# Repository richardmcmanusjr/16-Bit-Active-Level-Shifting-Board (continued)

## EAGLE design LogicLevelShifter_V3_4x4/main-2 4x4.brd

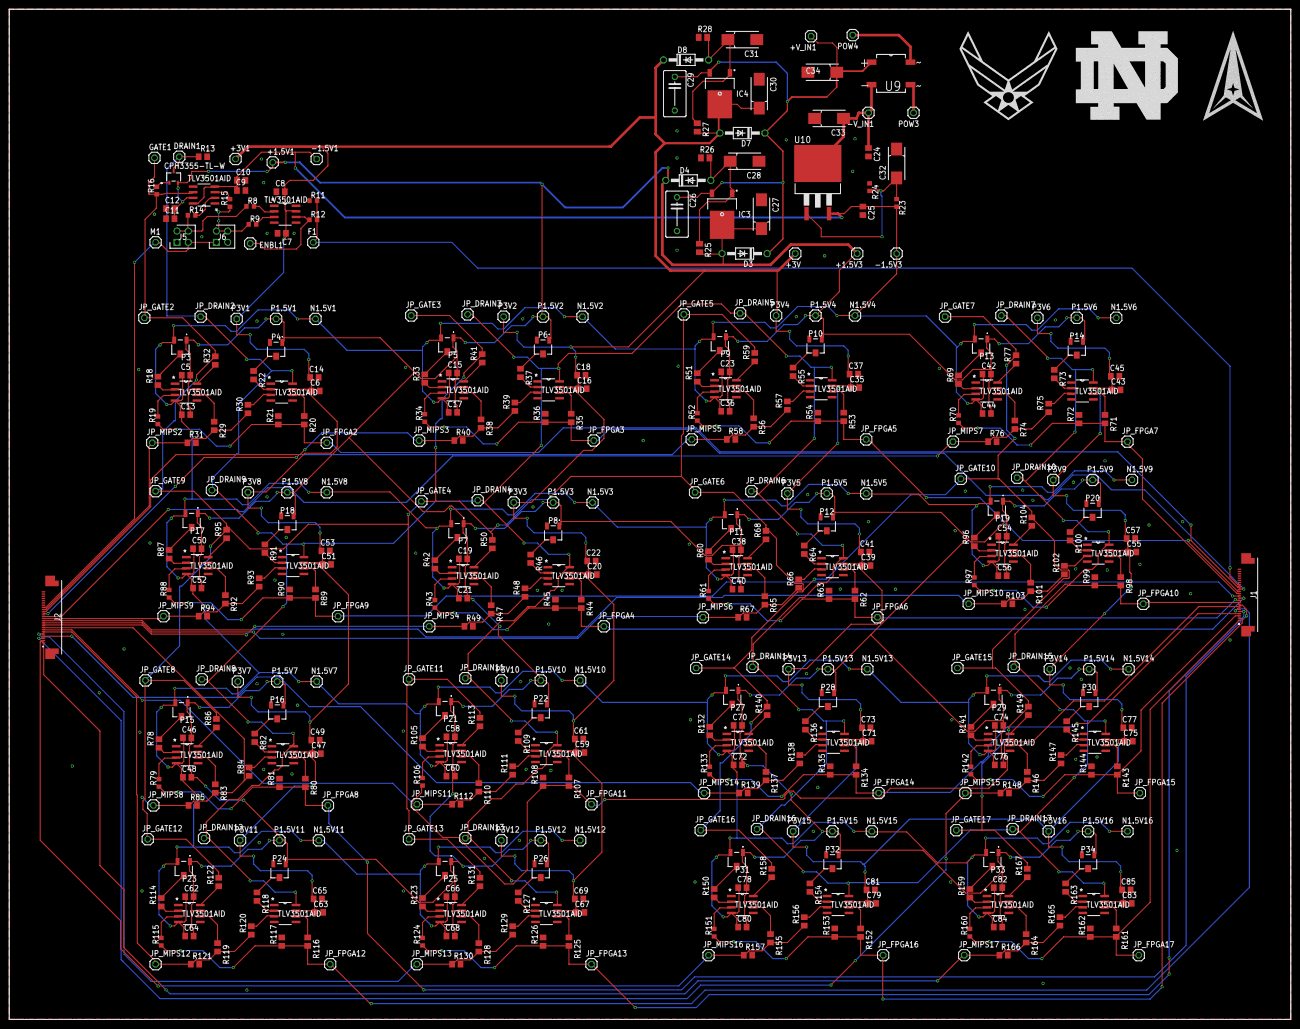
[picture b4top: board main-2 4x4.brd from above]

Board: 2 copper layers, 289.1 x 227.8 mm, 445 parts (0 on the bottom side), 199 nets.

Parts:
+1.5V1, +1.5V3, +3V, +3V1: 1X01
+V_IN1: 1X01
-1.5V1, -1.5V3: 1X01
-V_IN1: 1X01
C5, C6, C7, C8, C9, C10, C11, C12, C13, C14, C15, C16, C17, C18, C19, C20, C21, C22, C23, C35, C36, C37, C38, C39, C40, C41, C42, C43, C44, C45, C46, C47, C48, C49, C50, C51, C52, C53, C54, C55, C56, C57, C58, C59, C60, C61, C62, C63, C64, C65, C66, C67, C68, C69, C70, C71, C72, C73, C74, C75, C76, C77, C78, C79, C80, C81, C82, C83, C84, C85: C0805
C24: 10uF; C0805
C25: 0.1uF; C0805
C26, C29: 0.1uF; C075-052X106
C27, C30, C32: 1uF; 085CS_1AR
C28, C31, C33, C34: 10uF; 085CS_1AR
D3, D4, D7, D8: 1N4002; DO41-10
DRAIN1: 1X01
ENBL1: 1X01
F1: 1X01
GATE1: 1X01
IC3, IC4: LM317AMDT_NOPB; TO228P991X238-3N
J1, J2: 0524372471
J5, J6: 70287-1098; HDRV4W64P254_2X2_521X508X851P
JP_DRAIN2, JP_DRAIN3, JP_DRAIN4, JP_DRAIN5, JP_DRAIN6, JP_DRAIN7, JP_DRAIN8, JP_DRAIN9, JP_DRAIN10, JP_DRAIN11, JP_DRAIN12, JP_DRAIN13, JP_DRAIN14, JP_DRAIN15, JP_DRAIN16, JP_DRAIN17: 1X01
JP_FPGA2, JP_FPGA3, JP_FPGA4, JP_FPGA5, JP_FPGA6, JP_FPGA7, JP_FPGA8, JP_FPGA9, JP_FPGA10, JP_FPGA11, JP_FPGA12, JP_FPGA13, JP_FPGA14, JP_FPGA15, JP_FPGA16, JP_FPGA17: 1X01
JP_GATE2, JP_GATE3, JP_GATE4, JP_GATE5, JP_GATE6, JP_GATE7, JP_GATE8, JP_GATE9, JP_GATE10, JP_GATE11, JP_GATE12, JP_GATE13, JP_GATE14, JP_GATE15, JP_GATE16, JP_GATE17: 1X01
JP_MIPS2, JP_MIPS3, JP_MIPS4, JP_MIPS5, JP_MIPS6, JP_MIPS7, JP_MIPS8, JP_MIPS9, JP_MIPS10, JP_MIPS11, JP_MIPS12, JP_MIPS13, JP_MIPS14, JP_MIPS15, JP_MIPS16, JP_MIPS17: 1X01
M1: 1X01
N1.5V1, N1.5V2, N1.5V3, N1.5V4, N1.5V5, N1.5V6, N1.5V7, N1.5V8, N1.5V9, N1.5V10, N1.5V11, N1.5V12, N1.5V13, N1.5V14, N1.5V15, N1.5V16: 1X01
P1.5V1, P1.5V2, P1.5V3, P1.5V4, P1.5V5, P1.5V6, P1.5V7, P1.5V8, P1.5V9, P1.5V10, P1.5V11, P1.5V12, P1.5V13, P1.5V14, P1.5V15, P1.5V16, P3V1, P3V2, P3V3, P3V4, P3V5, P3V6, P3V7, P3V8, P3V9, P3V10, P3V11, P3V12, P3V13, P3V14, P3V15, P3V16: 1X01
P3, P4, P5, P6, P7, P8, P9, P10, P11, P12, P13, P14, P15, P16, P17, P18, P19, P20, P21, P22, P23, P24, P25, P26, P27, P28, P29, P30, P31, P32, P33, P34: SM-3TW102; SM3TW102
POW3, POW4: 1X01
R8, R9, R11, R12, R14, R15, R16: 220; R0603
R13: 51; R0805
R18, R22, R30, R33, R37, R39, R42, R46, R48, R51, R55, R57, R60, R64, R66, R69, R73, R75, R78, R82, R84, R87, R91, R93, R96, R100, R102, R105, R109, R111, R114, R118, R120, R123, R127, R129, R132, R136, R138, R141, R145, R147, R150, R154, R156, R159, R163, R165: 130; R0805
R19, R34, R43, R52, R61, R70, R79, R88, R97, R106, R115, R124, R133, R142, R151, R160: 130; R0603
R20, R21, R29, R31, R32, R35, R36, R38, R40, R41, R44, R45, R47, R49, R50, R53, R54, R56, R58, R59, R62, R63, R65, R67, R68, R71, R72, R74, R76, R77, R80, R81, R83, R85, R86, R89, R90, R92, R94, R95, R98, R99, R101, R103, R104, R107, R108, R110, R112, R113, R116, R117, R119, R121, R122, R125, R126, R128, R130, R131, R134, R135, R137, R139, R140, R143, R144, R146, R148, R149, R152, R153, R155, R157, R158, R161, R162, R164, R166, R167: 220; R0805
R23: 240; R0603
R24: 49.9; R0603
R25, R27: 240Ω; M0805
R26: 49Ω; M0805
R28: 390Ω; M0805
U3, U5, U6, U7, U8, U11, U12, U13, U14, U15, U16, U17, U18, U19, U20, U21, U22, U23, U24, U25, U26, U27, U28, U29, U30, U31, U32, U33, U34, U35, U36, U37, U38, U39: TLV3501AID; D8
U4: CPH3355-TL-W; CPH3_2P9X1P6_ONS
U9: DF10S; SOT508P985X260-4N
U10: MC79GENERICD2T; D2PAK-3

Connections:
+1.5V: +1.5V1.1, +1.5V3.1, C5.2, C11.2, C12.2, C13.2, C15.2, C17.2, C19.2, C21.2, C23.2, C27.+, C36.2, C38.2, C40.2, C42.2, C44.2, C46.2, C48.2, C50.2, C52.2, C54.2, C56.2, C58.2, C60.2, C62.2, C64.2, C66.2, C68.2, C70.2, C72.2, C74.2, C76.2, C78.2, C80.2, C82.2, C84.2, D3.A, D4.C, IC3.4, P1.5V1.1, P1.5V2.1, P1.5V3.1, P1.5V4.1, P1.5V5.1, P1.5V6.1, P1.5V7.1, P1.5V8.1, P1.5V9.1, P1.5V10.1, P1.5V11.1, P1.5V12.1, P1.5V13.1, P1.5V14.1, P1.5V15.1, P1.5V16.1, P3.1, P4.1, P5.1, P6.1, P7.1, P8.1, P9.1, P10.1, P11.1, P12.1, P13.1, P14.1, P15.1, P16.1, P17.1, P18.1, P19.1, P20.1, P21.1, P22.1, P23.1, P24.1, P25.1, P26.1, P27.1, P28.1, P29.1, P30.1, P31.1, P32.1, P33.1, P34.1, R25.2, U3.7, U4.2, U6.7, U8.7, U12.7, U14.7, U16.7, U18.7, U20.7, U22.7, U24.7, U26.7, U28.7, U30.7, U32.7, U34.7, U36.7, U38.7
+3V: +3V.1, +3V1.1, C6.1, C7.2, C8.2, C14.1, C16.1, C18.1, C20.1, C22.1, C30.+, C35.1, C37.1, C39.1, C41.1, C43.1, C45.1, C47.1, C49.1, C51.1, C53.1, C55.1, C57.1, C59.1, C61.1, C63.1, C65.1, C67.1, C69.1, C71.1, C73.1, C75.1, C77.1, C79.1, C81.1, C83.1, C85.1, D7.A, D8.C, IC4.4, P3V1.1, P3V2.1, P3V3.1, P3V4.1, P3V5.1, P3V6.1, P3V7.1, P3V8.1, P3V9.1, P3V10.1, P3V11.1, P3V12.1, P3V13.1, P3V14.1, P3V15.1, P3V16.1, R27.2, U5.7, U7.7, U11.7, U13.7, U15.7, U17.7, U19.7, U21.7, U23.7, U25.7, U27.7, U29.7, U31.7, U33.7, U35.7, U37.7, U39.7
-1.5V: -1.5V1.1, -1.5V3.1, C5.1, C9.1, C10.1, C13.1, C15.1, C17.1, C19.1, C21.1, C23.1, C25.1, C36.1, C38.1, C40.1, C42.1, C44.1, C46.1, C48.1, C50.1, C52.1, C54.1, C56.1, C58.1, C60.1, C62.1, C64.1, C66.1, C68.1, C70.1, C72.1, C74.1, C76.1, C78.1, C80.1, C82.1, C84.1, N1.5V1.1, N1.5V2.1, N1.5V3.1, N1.5V4.1, N1.5V5.1, N1.5V6.1, N1.5V7.1, N1.5V8.1, N1.5V9.1, N1.5V10.1, N1.5V11.1, N1.5V12.1, N1.5V13.1, N1.5V14.1, N1.5V15.1, N1.5V16.1, P3.3, P5.3, P7.3, P9.3, P11.3, P13.3, P15.3, P17.3, P19.3, P21.3, P23.3, P25.3, P27.3, P29.3, P31.3, P33.3, R23.2, U3.4, U6.4, U6.8, U8.4, U10.3, U12.4, U14.4, U16.4, U18.4, U20.4, U22.4, U24.4, U26.4, U28.4, U30.4, U32.4, U34.4, U36.4, U38.4
DIR_GATE: GATE1.1, JP_GATE2.1, JP_GATE3.1, JP_GATE4.1, JP_GATE5.1, JP_GATE6.1, JP_GATE7.1, JP_GATE8.1, JP_GATE9.1, JP_GATE10.1, JP_GATE11.1, JP_GATE12.1, JP_GATE13.1, JP_GATE14.1, JP_GATE15.1, JP_GATE16.1, JP_GATE17.1, R16.1, R32.2, R41.2, R50.2, R59.2, R68.2, R77.2, R86.2, R95.2, R104.2, R113.2, R122.2, R131.2, R140.2, R149.2, R158.2, R167.2, U6.6
F1: J1.1, JP_FPGA17.1, R160.1, R161.2, R162.1
F2: J1.2, JP_FPGA16.1, R151.1, R152.2, R153.1
F3: J1.3, JP_FPGA15.1, R142.1, R143.2, R144.1
F4: J1.4, JP_FPGA14.1, R133.1, R134.2, R135.1
F5: J1.5, JP_FPGA13.1, R124.1, R125.2, R126.1
F6: J1.6, JP_FPGA12.1, R115.1, R116.2, R117.1
F7: J1.7, JP_FPGA11.1, R106.1, R107.2, R108.1
F8: J1.8, JP_FPGA8.1, R79.1, R80.2, R81.1
F9: J1.9, JP_FPGA10.1, R97.1, R98.2, R99.1
F10: J1.10, JP_FPGA6.1, R61.1, R62.2, R63.1
F11: J1.11, JP_FPGA4.1, R43.1, R44.2, R45.1
F12: J1.12, JP_FPGA9.1, R88.1, R89.2, R90.1
F13: J1.13, JP_FPGA7.1, R70.1, R71.2, R72.1
F14: J1.14, JP_FPGA5.1, R52.1, R53.2, R54.1
F15: J1.15, JP_FPGA3.1, R34.1, R35.2, R36.1
F16: J1.16, JP_FPGA2.1, R19.1, R20.2, R21.1
F17: F1.1, J1.17, R11.2, R12.2
GND: C6.2, C7.1, C8.1, C9.2, C10.2, C11.1, C12.1, C14.2, C16.2, C18.2, C20.2, C22.2, C24.2, C25.2, C26.2, C27.-, C28.-, C29.2, C30.-, C31.-, C32.+, C33.+, C34.-, C35.2, C37.2, C39.2, C41.2, C43.2, C45.2, C47.2, C49.2, C51.2, C53.2, C55.2, C57.2, C59.2, C61.2, C63.2, C65.2, C67.2, C69.2, C71.2, C73.2, C75.2, C77.2, C79.2, C81.2, C83.2, C85.2, J1.MP1, J1.MP2, J1.MP3, J1.MP4, J2.MP1, J2.MP2, J2.MP3, J2.MP4, J5.1, J6.3, P4.3, P6.3, P8.3, P10.3, P12.3, P14.3, P16.3, P18.3, P20.3, P22.3, P24.3, P26.3, P28.3, P30.3, P32.3, P34.3, R11.1, R13.2, R21.2, R24.1, R26.1, R28.1, R31.2, R36.2, R40.2, R45.2, R49.2, R54.2, R58.2, R63.2, R67.2, R72.2, R76.2, R81.2, R85.2, R90.2, R94.2, R99.2, R103.2, R108.2, R112.2, R117.2, R121.2, R126.2, R130.2, R135.2, R139.2, R144.2, R148.2, R153.2, R157.2, R162.2, R166.2, U5.4, U5.8, U7.4, U11.4, U13.4, U15.4, U17.4, U19.4, U21.4, U23.4, U25.4, U27.4, U29.4, U31.4, U33.4, U35.4, U37.4, U39.4
INPPOS1: +V_IN1.1, C26.1, C29.1, C34.+, D3.C, D7.C, IC3.3, IC4.3, U9.1
INV_DIR_DRAIN: DRAIN1.1, JP_DRAIN2.1, JP_DRAIN3.1, JP_DRAIN4.1, JP_DRAIN5.1, JP_DRAIN6.1, JP_DRAIN7.1, JP_DRAIN8.1, JP_DRAIN9.1, JP_DRAIN10.1, JP_DRAIN11.1, JP_DRAIN12.1, JP_DRAIN13.1, JP_DRAIN14.1, JP_DRAIN15.1, JP_DRAIN16.1, JP_DRAIN17.1, R13.1, U4.3, U7.8, U11.8, U13.8, U15.8, U17.8, U19.8, U21.8, U23.8, U25.8, U27.8, U29.8, U31.8, U33.8, U35.8, U37.8, U39.8
IN_2: POW3.1, U9.3
M1: J2.1, JP_MIPS17.1, R164.2, R165.1, R166.1
M2: J2.2, JP_MIPS16.1, R155.2, R156.1, R157.1
M3: J2.3, JP_MIPS15.1, R146.2, R147.1, R148.1
M4: J2.4, JP_MIPS14.1, R137.2, R138.1, R139.1
M5: J2.5, JP_MIPS13.1, R128.2, R129.1, R130.1
M6: J2.6, JP_MIPS12.1, R119.2, R120.1, R121.1
M7: J2.7, JP_MIPS11.1, R110.2, R111.1, R112.1
M8: J2.8, JP_MIPS8.1, R83.2, R84.1, R85.1
M9: J2.9, JP_MIPS10.1, R101.2, R102.1, R103.1
M10: J2.10, JP_MIPS6.1, R65.2, R66.1, R67.1
M11: J2.11, JP_MIPS4.1, R47.2, R48.1, R49.1
M12: J2.12, JP_MIPS9.1, R92.2, R93.1, R94.1
M13: J2.13, JP_MIPS7.1, R74.2, R75.1, R76.1
M14: J2.14, JP_MIPS5.1, R56.2, R57.1, R58.1
M15: J2.15, JP_MIPS3.1, R38.2, R39.1, R40.1
M16: J2.16, JP_MIPS2.1, R29.2, R30.1, R31.1
M17: J2.17, J5.3, J6.1, M1.1
unnamed: P3.2, R18.2
unnamed: R18.1, U3.2
unnamed: R19.2, U3.3
unnamed: R20.1, U7.6
unnamed: P4.2, R22.1
unnamed: R22.2, U7.2
unnamed: R8.2, U5.2
unnamed: R30.2, U7.3
unnamed: R9.2, U5.3
unnamed: ENBL1.1, R12.1, U5.6
unnamed: J6.2, J6.4, R9.1, R15.1
unnamed: J5.2, J5.4, R8.1, R14.1
unnamed: R14.2, U6.2
unnamed: R15.2, U6.3
unnamed: R16.2, U4.1
unnamed: R29.1, U3.6
unnamed: R32.1, U3.8
unnamed: P5.2, R33.2
unnamed: R33.1, U8.2
unnamed: R34.2, U8.3
unnamed: C32.-, R23.1, R24.2, U10.1
unnamed: C28.+, D4.A, IC3.1, R25.1, R26.2
unnamed: C31.+, D8.A, IC4.1, R27.1, R28.2
unnamed: POW4.1, U9.4
unnamed: -V_IN1.1, C24.1, C33.-, U9.2, U10.4
unnamed: R35.1, U11.6
unnamed: P6.2, R37.1
unnamed: R37.2, U11.2
unnamed: R39.2, U11.3
unnamed: R38.1, U8.6
unnamed: R41.1, U8.8
unnamed: P7.2, R42.2
unnamed: R42.1, U12.2
unnamed: R43.2, U12.3
unnamed: R44.1, U13.6
unnamed: P8.2, R46.1
unnamed: R46.2, U13.2
unnamed: R48.2, U13.3
unnamed: R47.1, U12.6
unnamed: R50.1, U12.8
unnamed: P9.2, R51.2
unnamed: R51.1, U14.2
unnamed: R52.2, U14.3
unnamed: R53.1, U15.6
unnamed: P10.2, R55.1
unnamed: R55.2, U15.2
unnamed: R57.2, U15.3
unnamed: R56.1, U14.6
unnamed: R59.1, U14.8
unnamed: P11.2, R60.2
unnamed: R60.1, U16.2
unnamed: R61.2, U16.3
unnamed: R62.1, U17.6
unnamed: P12.2, R64.1
unnamed: R64.2, U17.2
unnamed: R66.2, U17.3
unnamed: R65.1, U16.6
unnamed: R68.1, U16.8
unnamed: P13.2, R69.2
unnamed: R69.1, U18.2
unnamed: R70.2, U18.3
unnamed: R71.1, U19.6
unnamed: P14.2, R73.1
unnamed: R73.2, U19.2
unnamed: R75.2, U19.3
unnamed: R74.1, U18.6
unnamed: R77.1, U18.8
unnamed: P15.2, R78.2
unnamed: R78.1, U20.2
unnamed: R79.2, U20.3
unnamed: R80.1, U21.6
unnamed: P16.2, R82.1
unnamed: R82.2, U21.2
unnamed: R84.2, U21.3
unnamed: R83.1, U20.6
unnamed: R86.1, U20.8
unnamed: P17.2, R87.2
unnamed: R87.1, U22.2
unnamed: R88.2, U22.3
unnamed: R89.1, U23.6
unnamed: P18.2, R91.1
unnamed: R91.2, U23.2
unnamed: R93.2, U23.3
unnamed: R92.1, U22.6
unnamed: R95.1, U22.8
unnamed: P19.2, R96.2
unnamed: R96.1, U24.2
unnamed: R97.2, U24.3
unnamed: R98.1, U25.6
unnamed: P20.2, R100.1
unnamed: R100.2, U25.2
unnamed: R102.2, U25.3
unnamed: R101.1, U24.6
unnamed: R104.1, U24.8
unnamed: P21.2, R105.2
unnamed: R105.1, U26.2
unnamed: R106.2, U26.3
unnamed: R107.1, U27.6
unnamed: P22.2, R109.1
unnamed: R109.2, U27.2
unnamed: R111.2, U27.3
unnamed: R110.1, U26.6
unnamed: R113.1, U26.8
unnamed: P23.2, R114.2
unnamed: R114.1, U28.2
unnamed: R115.2, U28.3
unnamed: R116.1, U29.6
unnamed: P24.2, R118.1
unnamed: R118.2, U29.2
unnamed: R120.2, U29.3
unnamed: R119.1, U28.6
unnamed: R122.1, U28.8
unnamed: P25.2, R123.2
unnamed: R123.1, U30.2
unnamed: R124.2, U30.3
unnamed: R125.1, U31.6
unnamed: P26.2, R127.1
unnamed: R127.2, U31.2
unnamed: R129.2, U31.3
unnamed: R128.1, U30.6
unnamed: R131.1, U30.8
unnamed: P27.2, R132.2
unnamed: R132.1, U32.2
unnamed: R133.2, U32.3
unnamed: R134.1, U33.6
unnamed: P28.2, R136.1
unnamed: R136.2, U33.2
unnamed: R138.2, U33.3
unnamed: R137.1, U32.6
unnamed: R140.1, U32.8
unnamed: P29.2, R141.2
unnamed: R141.1, U34.2
unnamed: R142.2, U34.3
unnamed: R143.1, U35.6
unnamed: P30.2, R145.1
unnamed: R145.2, U35.2
unnamed: R147.2, U35.3
unnamed: R146.1, U34.6
unnamed: R149.1, U34.8
unnamed: P31.2, R150.2
unnamed: R150.1, U36.2
unnamed: R151.2, U36.3
unnamed: R152.1, U37.6
unnamed: P32.2, R154.1
unnamed: R154.2, U37.2
unnamed: R156.2, U37.3
unnamed: R155.1, U36.6
unnamed: R158.1, U36.8
unnamed: P33.2, R159.2
unnamed: R159.1, U38.2
unnamed: R160.2, U38.3
unnamed: R161.1, U39.6
unnamed: P34.2, R163.1
unnamed: R163.2, U39.2
unnamed: R165.2, U39.3
unnamed: R164.1, U38.6
unnamed: R167.1, U38.8

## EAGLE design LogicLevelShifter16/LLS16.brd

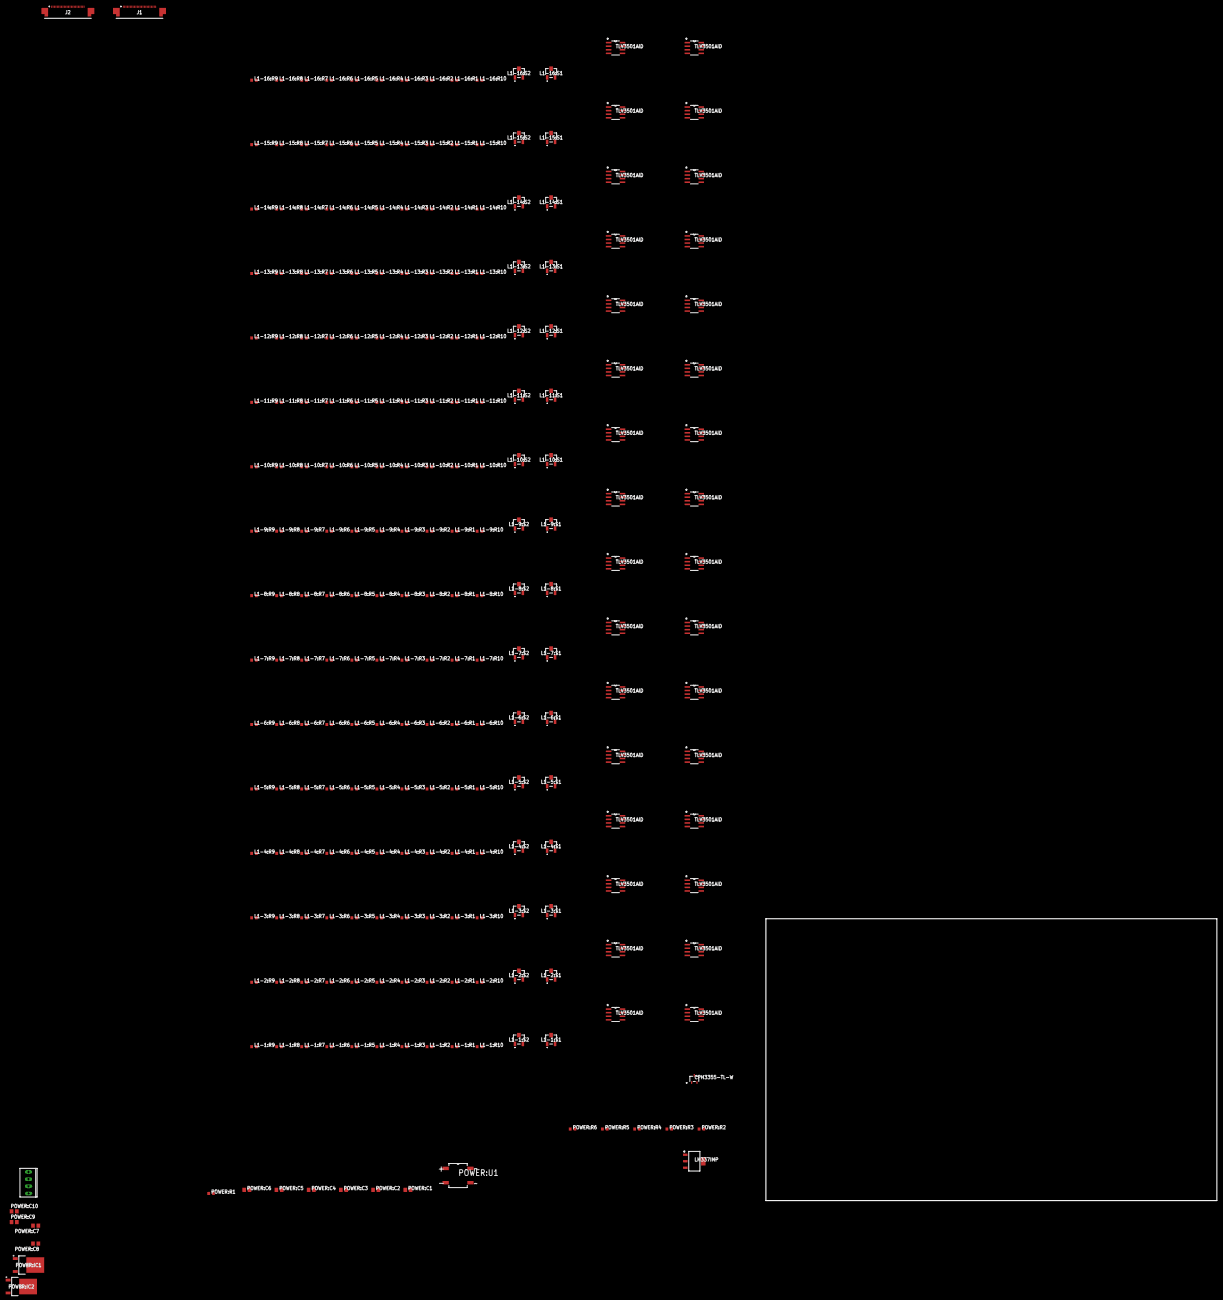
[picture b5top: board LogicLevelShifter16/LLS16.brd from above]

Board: 2 copper layers, 160.0 x 100.0 mm, 248 parts (0 on the bottom side), 204 nets, no tracks yet.

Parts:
J1, J2: 0524372471
L1-1:R1, L1-1:R2, L1-1:R6, L1-1:R8, L1-2:R1, L1-2:R2, L1-2:R6, L1-2:R8, L1-3:R1, L1-3:R2, L1-3:R6, L1-3:R8, L1-4:R1, L1-4:R2, L1-4:R6, L1-4:R8, L1-5:R1, L1-5:R2, L1-5:R6, L1-5:R8, L1-6:R1, L1-6:R2, L1-6:R6, L1-6:R8, L1-7:R1, L1-7:R2, L1-7:R6, L1-7:R8, L1-8:R1, L1-8:R2, L1-8:R6, L1-8:R8, L1-9:R1, L1-9:R2, L1-9:R6, L1-9:R8, L1-10:R1, L1-10:R2, L1-10:R6, L1-10:R8, L1-11:R1, L1-11:R2, L1-11:R6, L1-11:R8, L1-12:R1, L1-12:R2, L1-12:R6, L1-12:R8, L1-13:R1, L1-13:R2, L1-13:R6, L1-13:R8, L1-14:R1, L1-14:R2, L1-14:R6, L1-14:R8, L1-15:R1, L1-15:R2, L1-15:R6, L1-15:R8, L1-16:R1, L1-16:R2, L1-16:R6, L1-16:R8: 130; R0603
L1-1:R3, L1-1:R4, L1-1:R7, L1-1:R9, L1-1:R10, L1-2:R3, L1-2:R4, L1-2:R7, L1-2:R9, L1-2:R10, L1-3:R3, L1-3:R4, L1-3:R7, L1-3:R9, L1-3:R10, L1-4:R3, L1-4:R4, L1-4:R7, L1-4:R9, L1-4:R10, L1-5:R3, L1-5:R4, L1-5:R7, L1-5:R9, L1-5:R10, L1-6:R3, L1-6:R4, L1-6:R7, L1-6:R9, L1-6:R10, L1-7:R3, L1-7:R4, L1-7:R7, L1-7:R9, L1-7:R10, L1-8:R3, L1-8:R4, L1-8:R7, L1-8:R9, L1-8:R10, L1-9:R3, L1-9:R4, L1-9:R7, L1-9:R9, L1-9:R10, L1-10:R3, L1-10:R4, L1-10:R7, L1-10:R9, L1-10:R10, L1-11:R3, L1-11:R4, L1-11:R7, L1-11:R9, L1-11:R10, L1-12:R3, L1-12:R4, L1-12:R7, L1-12:R9, L1-12:R10, L1-13:R3, L1-13:R4, L1-13:R7, L1-13:R9, L1-13:R10, L1-14:R3, L1-14:R4, L1-14:R7, L1-14:R9, L1-14:R10, L1-15:R3, L1-15:R4, L1-15:R7, L1-15:R9, L1-15:R10, L1-16:R3, L1-16:R4, L1-16:R7, L1-16:R9, L1-16:R10: 220; R0603
L1-1:R5, L1-2:R5, L1-3:R5, L1-4:R5, L1-5:R5, L1-6:R5, L1-7:R5, L1-8:R5, L1-9:R5, L1-10:R5, L1-11:R5, L1-12:R5, L1-13:R5, L1-14:R5, L1-15:R5, L1-16:R5: 51; R0603
L1-1:S1, L1-1:S2, L1-2:S1, L1-2:S2, L1-3:S1, L1-3:S2, L1-4:S1, L1-4:S2, L1-5:S1, L1-5:S2, L1-6:S1, L1-6:S2, L1-7:S1, L1-7:S2, L1-8:S1, L1-8:S2, L1-9:S1, L1-9:S2, L1-10:S1, L1-10:S2, L1-11:S1, L1-11:S2, L1-12:S1, L1-12:S2, L1-13:S1, L1-13:S2, L1-14:S1, L1-14:S2, L1-15:S1, L1-15:S2, L1-16:S1, L1-16:S2: SM-3TW102; SM3TW102
L1-1:U1, L1-1:U2, L1-2:U1, L1-2:U2, L1-3:U1, L1-3:U2, L1-4:U1, L1-4:U2, L1-5:U1, L1-5:U2, L1-6:U1, L1-6:U2, L1-7:U1, L1-7:U2, L1-8:U1, L1-8:U2, L1-9:U1, L1-9:U2, L1-10:U1, L1-10:U2, L1-11:U1, L1-11:U2, L1-12:U1, L1-12:U2, L1-13:U1, L1-13:U2, L1-14:U1, L1-14:U2, L1-15:U1, L1-15:U2, L1-16:U1, L1-16:U2: TLV3501AID; D8
POWER:C1, POWER:C2, POWER:C3: 10uF; C0805
POWER:C4, POWER:C5, POWER:C6: 0.1uF; C0805
POWER:C7, POWER:C9: 0.1 uF; C0805
POWER:C8, POWER:C10: 2.2 uF; C0805
POWER:IC1, POWER:IC2: LM317AMDT_NOPB; TO228P991X238-3N
POWER:R1, POWER:R3, POWER:R5: 240; R0603
POWER:R2, POWER:R4, POWER:R6: 49.9; R0603
POWER:U1: DF10S; SOT508P985X260-4N
POWER:U2: LM337IMP; MP04A_TEX
U1: CPH3355-TL-W; CPH3_2P9X1P6_ONS
U$1: CONNHEADERVERT4POS2.54MM

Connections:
+1.5V: L1-1:S1.3, L1-1:S2.1, L1-1:U1.7, L1-2:S1.3, L1-2:S2.1, L1-2:U1.7, L1-3:S1.3, L1-3:S2.1, L1-3:U1.7, L1-4:S1.3, L1-4:S2.1, L1-4:U1.7, L1-5:S1.3, L1-5:S2.1, L1-5:U1.7, L1-6:S1.3, L1-6:S2.1, L1-6:U1.7, L1-7:S1.3, L1-7:S2.1, L1-7:U1.7, L1-8:S1.3, L1-8:S2.1, L1-8:U1.7, L1-9:S1.3, L1-9:S2.1, L1-9:U1.7, L1-10:S1.3, L1-10:S2.1, L1-10:U1.7, L1-11:S1.3, L1-11:S2.1, L1-11:U1.7, L1-12:S1.3, L1-12:S2.1, L1-12:U1.7, L1-13:S1.3, L1-13:S2.1, L1-13:U1.7, L1-14:S1.3, L1-14:S2.1, L1-14:U1.7, L1-15:S1.3, L1-15:S2.1, L1-15:U1.7, L1-16:S1.3, L1-16:S2.1, L1-16:U1.7, POWER:C5.1, POWER:C9.1, POWER:C10.1, POWER:IC1.4, POWER:R3.2, U1.2
+3V: L1-1:U2.7, L1-2:U2.7, L1-3:U2.7, L1-4:U2.7, L1-5:U2.7, L1-6:U2.7, L1-7:U2.7, L1-8:U2.7, L1-9:U2.7, L1-10:U2.7, L1-11:U2.7, L1-12:U2.7, L1-13:U2.7, L1-14:U2.7, L1-15:U2.7, L1-16:U2.7, POWER:C6.1, POWER:C7.1, POWER:C8.1, POWER:IC2.4, POWER:R5.2
+5V: POWER:U1.4, U$1.4
-1.5V: L1-1:S1.1, L1-1:U1.4, L1-2:S1.1, L1-2:U1.4, L1-3:S1.1, L1-3:U1.4, L1-4:S1.1, L1-4:U1.4, L1-5:S1.1, L1-5:U1.4, L1-6:S1.1, L1-6:U1.4, L1-7:S1.1, L1-7:U1.4, L1-8:S1.1, L1-8:U1.4, L1-9:S1.1, L1-9:U1.4, L1-10:S1.1, L1-10:U1.4, L1-11:S1.1, L1-11:U1.4, L1-12:S1.1, L1-12:U1.4, L1-13:S1.1, L1-13:U1.4, L1-14:S1.1, L1-14:U1.4, L1-15:S1.1, L1-15:U1.4, L1-16:S1.1, L1-16:U1.4, POWER:C4.1, POWER:C9.2, POWER:C10.2, POWER:R1.2, POWER:U2.3
D: L1-1:R5.1, L1-1:U2.8, L1-2:R5.1, L1-2:U2.8, L1-3:R5.1, L1-3:U2.8, L1-4:R5.1, L1-4:U2.8, L1-5:R5.1, L1-5:U2.8, L1-6:R5.1, L1-6:U2.8, L1-7:R5.1, L1-7:U2.8, L1-8:R5.1, L1-8:U2.8, L1-9:R5.1, L1-9:U2.8, L1-10:R5.1, L1-10:U2.8, L1-11:R5.1, L1-11:U2.8, L1-12:R5.1, L1-12:U2.8, L1-13:R5.1, L1-13:U2.8, L1-14:R5.1, L1-14:U2.8, L1-15:R5.1, L1-15:U2.8, L1-16:R5.1, L1-16:U2.8, U1.3
F1: J1.1, L1-1:R2.1, L1-1:R3.2, L1-1:R4.1
F2: J1.2, L1-2:R2.1, L1-2:R3.2, L1-2:R4.1
F3: J1.3, L1-3:R2.1, L1-3:R3.2, L1-3:R4.1
F4: J1.4, L1-4:R2.1, L1-4:R3.2, L1-4:R4.1
F5: J1.5, L1-5:R2.1, L1-5:R3.2, L1-5:R4.1
F6: J1.6, L1-6:R2.1, L1-6:R3.2, L1-6:R4.1
F7: J1.7, L1-7:R2.1, L1-7:R3.2, L1-7:R4.1
F8: J1.8, L1-8:R2.1, L1-8:R3.2, L1-8:R4.1
F9: J1.9, L1-9:R2.1, L1-9:R3.2, L1-9:R4.1
F10: J1.10, L1-10:R2.1, L1-10:R3.2, L1-10:R4.1
F11: J1.11, L1-11:R2.1, L1-11:R3.2, L1-11:R4.1
F12: J1.12, L1-12:R2.1, L1-12:R3.2, L1-12:R4.1
F13: J1.13, L1-13:R2.1, L1-13:R3.2, L1-13:R4.1
F14: J1.14, L1-14:R2.1, L1-14:R3.2, L1-14:R4.1
F15: J1.15, L1-15:R2.1, L1-15:R3.2, L1-15:R4.1
F16: J1.16, L1-16:R2.1, L1-16:R3.2, L1-16:R4.1
G: L1-1:R10.2, L1-2:R10.2, L1-3:R10.2, L1-4:R10.2, L1-5:R10.2, L1-6:R10.2, L1-7:R10.2, L1-8:R10.2, L1-9:R10.2, L1-10:R10.2, L1-11:R10.2, L1-12:R10.2, L1-13:R10.2, L1-14:R10.2, L1-15:R10.2, L1-16:R10.2, U1.1
GND: POWER:C1.2, POWER:C2.2, POWER:C3.2, POWER:C4.2, POWER:C5.2, POWER:C6.2, POWER:C7.2, POWER:C8.2, POWER:R2.1, POWER:R4.1, POWER:R6.1, U$1.2, U$1.3
L1-1:GND!: L1-1:R4.2, L1-1:R5.2, L1-1:R9.2, L1-1:S2.3, L1-1:U2.4
L1-1:N$1: L1-1:R1.2, L1-1:S1.2
L1-1:N$2: L1-1:R1.1, L1-1:U1.2
L1-1:N$3: L1-1:R2.2, L1-1:U1.3
L1-1:N$5: L1-1:R3.1, L1-1:U2.6
L1-1:N$6: L1-1:R6.1, L1-1:S2.2
L1-1:N$7: L1-1:R6.2, L1-1:U2.2
L1-1:N$8: L1-1:R8.2, L1-1:U2.3
L1-1:N$10: L1-1:R7.1, L1-1:U1.6
L1-1:N$11: L1-1:R10.1, L1-1:U1.8
L1-2:GND!: L1-2:R4.2, L1-2:R5.2, L1-2:R9.2, L1-2:S2.3, L1-2:U2.4
L1-2:N$1: L1-2:R1.2, L1-2:S1.2
L1-2:N$2: L1-2:R1.1, L1-2:U1.2
L1-2:N$3: L1-2:R2.2, L1-2:U1.3
L1-2:N$5: L1-2:R3.1, L1-2:U2.6
L1-2:N$6: L1-2:R6.1, L1-2:S2.2
L1-2:N$7: L1-2:R6.2, L1-2:U2.2
L1-2:N$8: L1-2:R8.2, L1-2:U2.3
L1-2:N$10: L1-2:R7.1, L1-2:U1.6
L1-2:N$11: L1-2:R10.1, L1-2:U1.8
L1-3:GND!: L1-3:R4.2, L1-3:R5.2, L1-3:R9.2, L1-3:S2.3, L1-3:U2.4
L1-3:N$1: L1-3:R1.2, L1-3:S1.2
L1-3:N$2: L1-3:R1.1, L1-3:U1.2
L1-3:N$3: L1-3:R2.2, L1-3:U1.3
L1-3:N$5: L1-3:R3.1, L1-3:U2.6
L1-3:N$6: L1-3:R6.1, L1-3:S2.2
L1-3:N$7: L1-3:R6.2, L1-3:U2.2
L1-3:N$8: L1-3:R8.2, L1-3:U2.3
L1-3:N$10: L1-3:R7.1, L1-3:U1.6
L1-3:N$11: L1-3:R10.1, L1-3:U1.8
L1-4:GND!: L1-4:R4.2, L1-4:R5.2, L1-4:R9.2, L1-4:S2.3, L1-4:U2.4
L1-4:N$1: L1-4:R1.2, L1-4:S1.2
L1-4:N$2: L1-4:R1.1, L1-4:U1.2
L1-4:N$3: L1-4:R2.2, L1-4:U1.3
L1-4:N$5: L1-4:R3.1, L1-4:U2.6
L1-4:N$6: L1-4:R6.1, L1-4:S2.2
L1-4:N$7: L1-4:R6.2, L1-4:U2.2
L1-4:N$8: L1-4:R8.2, L1-4:U2.3
L1-4:N$10: L1-4:R7.1, L1-4:U1.6
L1-4:N$11: L1-4:R10.1, L1-4:U1.8
L1-5:GND!: L1-5:R4.2, L1-5:R5.2, L1-5:R9.2, L1-5:S2.3, L1-5:U2.4
L1-5:N$1: L1-5:R1.2, L1-5:S1.2
L1-5:N$2: L1-5:R1.1, L1-5:U1.2
L1-5:N$3: L1-5:R2.2, L1-5:U1.3
L1-5:N$5: L1-5:R3.1, L1-5:U2.6
L1-5:N$6: L1-5:R6.1, L1-5:S2.2
L1-5:N$7: L1-5:R6.2, L1-5:U2.2
L1-5:N$8: L1-5:R8.2, L1-5:U2.3
L1-5:N$10: L1-5:R7.1, L1-5:U1.6
L1-5:N$11: L1-5:R10.1, L1-5:U1.8
L1-6:GND!: L1-6:R4.2, L1-6:R5.2, L1-6:R9.2, L1-6:S2.3, L1-6:U2.4
L1-6:N$1: L1-6:R1.2, L1-6:S1.2
L1-6:N$2: L1-6:R1.1, L1-6:U1.2
L1-6:N$3: L1-6:R2.2, L1-6:U1.3
L1-6:N$5: L1-6:R3.1, L1-6:U2.6
L1-6:N$6: L1-6:R6.1, L1-6:S2.2
L1-6:N$7: L1-6:R6.2, L1-6:U2.2
L1-6:N$8: L1-6:R8.2, L1-6:U2.3
L1-6:N$10: L1-6:R7.1, L1-6:U1.6
L1-6:N$11: L1-6:R10.1, L1-6:U1.8
L1-7:GND!: L1-7:R4.2, L1-7:R5.2, L1-7:R9.2, L1-7:S2.3, L1-7:U2.4
L1-7:N$1: L1-7:R1.2, L1-7:S1.2
L1-7:N$2: L1-7:R1.1, L1-7:U1.2
L1-7:N$3: L1-7:R2.2, L1-7:U1.3
L1-7:N$5: L1-7:R3.1, L1-7:U2.6
L1-7:N$6: L1-7:R6.1, L1-7:S2.2
L1-7:N$7: L1-7:R6.2, L1-7:U2.2
L1-7:N$8: L1-7:R8.2, L1-7:U2.3
L1-7:N$10: L1-7:R7.1, L1-7:U1.6
L1-7:N$11: L1-7:R10.1, L1-7:U1.8
L1-8:GND!: L1-8:R4.2, L1-8:R5.2, L1-8:R9.2, L1-8:S2.3, L1-8:U2.4
L1-8:N$1: L1-8:R1.2, L1-8:S1.2
L1-8:N$2: L1-8:R1.1, L1-8:U1.2
L1-8:N$3: L1-8:R2.2, L1-8:U1.3
L1-8:N$5: L1-8:R3.1, L1-8:U2.6
L1-8:N$6: L1-8:R6.1, L1-8:S2.2
L1-8:N$7: L1-8:R6.2, L1-8:U2.2
L1-8:N$8: L1-8:R8.2, L1-8:U2.3
L1-8:N$10: L1-8:R7.1, L1-8:U1.6
L1-8:N$11: L1-8:R10.1, L1-8:U1.8
L1-9:GND!: L1-9:R4.2, L1-9:R5.2, L1-9:R9.2, L1-9:S2.3, L1-9:U2.4
L1-9:N$1: L1-9:R1.2, L1-9:S1.2
L1-9:N$2: L1-9:R1.1, L1-9:U1.2
L1-9:N$3: L1-9:R2.2, L1-9:U1.3
L1-9:N$5: L1-9:R3.1, L1-9:U2.6
L1-9:N$6: L1-9:R6.1, L1-9:S2.2
L1-9:N$7: L1-9:R6.2, L1-9:U2.2
L1-9:N$8: L1-9:R8.2, L1-9:U2.3
L1-9:N$10: L1-9:R7.1, L1-9:U1.6
L1-9:N$11: L1-9:R10.1, L1-9:U1.8
L1-10:GND!: L1-10:R4.2, L1-10:R5.2, L1-10:R9.2, L1-10:S2.3, L1-10:U2.4
L1-10:N$1: L1-10:R1.2, L1-10:S1.2
L1-10:N$2: L1-10:R1.1, L1-10:U1.2
L1-10:N$3: L1-10:R2.2, L1-10:U1.3
L1-10:N$5: L1-10:R3.1, L1-10:U2.6
L1-10:N$6: L1-10:R6.1, L1-10:S2.2
L1-10:N$7: L1-10:R6.2, L1-10:U2.2
L1-10:N$8: L1-10:R8.2, L1-10:U2.3
L1-10:N$10: L1-10:R7.1, L1-10:U1.6
L1-10:N$11: L1-10:R10.1, L1-10:U1.8
L1-11:GND!: L1-11:R4.2, L1-11:R5.2, L1-11:R9.2, L1-11:S2.3, L1-11:U2.4
L1-11:N$1: L1-11:R1.2, L1-11:S1.2
L1-11:N$2: L1-11:R1.1, L1-11:U1.2
L1-11:N$3: L1-11:R2.2, L1-11:U1.3
L1-11:N$5: L1-11:R3.1, L1-11:U2.6
L1-11:N$6: L1-11:R6.1, L1-11:S2.2
L1-11:N$7: L1-11:R6.2, L1-11:U2.2
L1-11:N$8: L1-11:R8.2, L1-11:U2.3
L1-11:N$10: L1-11:R7.1, L1-11:U1.6
L1-11:N$11: L1-11:R10.1, L1-11:U1.8
L1-12:GND!: L1-12:R4.2, L1-12:R5.2, L1-12:R9.2, L1-12:S2.3, L1-12:U2.4
L1-12:N$1: L1-12:R1.2, L1-12:S1.2
L1-12:N$2: L1-12:R1.1, L1-12:U1.2
L1-12:N$3: L1-12:R2.2, L1-12:U1.3
L1-12:N$5: L1-12:R3.1, L1-12:U2.6
L1-12:N$6: L1-12:R6.1, L1-12:S2.2
L1-12:N$7: L1-12:R6.2, L1-12:U2.2
L1-12:N$8: L1-12:R8.2, L1-12:U2.3
L1-12:N$10: L1-12:R7.1, L1-12:U1.6
L1-12:N$11: L1-12:R10.1, L1-12:U1.8
L1-13:GND!: L1-13:R4.2, L1-13:R5.2, L1-13:R9.2, L1-13:S2.3, L1-13:U2.4
L1-13:N$1: L1-13:R1.2, L1-13:S1.2
L1-13:N$2: L1-13:R1.1, L1-13:U1.2
L1-13:N$3: L1-13:R2.2, L1-13:U1.3
L1-13:N$5: L1-13:R3.1, L1-13:U2.6
L1-13:N$6: L1-13:R6.1, L1-13:S2.2
L1-13:N$7: L1-13:R6.2, L1-13:U2.2
L1-13:N$8: L1-13:R8.2, L1-13:U2.3
L1-13:N$10: L1-13:R7.1, L1-13:U1.6
L1-13:N$11: L1-13:R10.1, L1-13:U1.8
L1-14:GND!: L1-14:R4.2, L1-14:R5.2, L1-14:R9.2, L1-14:S2.3, L1-14:U2.4
L1-14:N$1: L1-14:R1.2, L1-14:S1.2
L1-14:N$2: L1-14:R1.1, L1-14:U1.2
L1-14:N$3: L1-14:R2.2, L1-14:U1.3
L1-14:N$5: L1-14:R3.1, L1-14:U2.6
L1-14:N$6: L1-14:R6.1, L1-14:S2.2
L1-14:N$7: L1-14:R6.2, L1-14:U2.2
L1-14:N$8: L1-14:R8.2, L1-14:U2.3
L1-14:N$10: L1-14:R7.1, L1-14:U1.6
L1-14:N$11: L1-14:R10.1, L1-14:U1.8
L1-15:GND!: L1-15:R4.2, L1-15:R5.2, L1-15:R9.2, L1-15:S2.3, L1-15:U2.4
L1-15:N$1: L1-15:R1.2, L1-15:S1.2
L1-15:N$2: L1-15:R1.1, L1-15:U1.2
L1-15:N$3: L1-15:R2.2, L1-15:U1.3
L1-15:N$5: L1-15:R3.1, L1-15:U2.6
L1-15:N$6: L1-15:R6.1, L1-15:S2.2
L1-15:N$7: L1-15:R6.2, L1-15:U2.2
L1-15:N$8: L1-15:R8.2, L1-15:U2.3
L1-15:N$10: L1-15:R7.1, L1-15:U1.6
L1-15:N$11: L1-15:R10.1, L1-15:U1.8
L1-16:GND!: L1-16:R4.2, L1-16:R5.2, L1-16:R9.2, L1-16:S2.3, L1-16:U2.4
L1-16:N$1: L1-16:R1.2, L1-16:S1.2
L1-16:N$2: L1-16:R1.1, L1-16:U1.2
L1-16:N$3: L1-16:R2.2, L1-16:U1.3
L1-16:N$5: L1-16:R3.1, L1-16:U2.6
L1-16:N$6: L1-16:R6.1, L1-16:S2.2
L1-16:N$7: L1-16:R6.2, L1-16:U2.2
L1-16:N$8: L1-16:R8.2, L1-16:U2.3
L1-16:N$10: L1-16:R7.1, L1-16:U1.6
L1-16:N$11: L1-16:R10.1, L1-16:U1.8
M1: J2.1, L1-1:R7.2, L1-1:R8.1, L1-1:R9.1
M2: J2.2, L1-2:R7.2, L1-2:R8.1, L1-2:R9.1
M3: J2.3, L1-3:R7.2, L1-3:R8.1, L1-3:R9.1
M4: J2.4, L1-4:R7.2, L1-4:R8.1, L1-4:R9.1
M5: J2.5, L1-5:R7.2, L1-5:R8.1, L1-5:R9.1
M6: J2.6, L1-6:R7.2, L1-6:R8.1, L1-6:R9.1
M7: J2.7, L1-7:R7.2, L1-7:R8.1, L1-7:R9.1
M8: J2.8, L1-8:R7.2, L1-8:R8.1, L1-8:R9.1
M9: J2.9, L1-9:R7.2, L1-9:R8.1, L1-9:R9.1
M10: J2.10, L1-10:R7.2, L1-10:R8.1, L1-10:R9.1
M11: J2.11, L1-11:R7.2, L1-11:R8.1, L1-11:R9.1
M12: J2.12, L1-12:R7.2, L1-12:R8.1, L1-12:R9.1
M13: J2.13, L1-13:R7.2, L1-13:R8.1, L1-13:R9.1
M14: J2.14, L1-14:R7.2, L1-14:R8.1, L1-14:R9.1
M15: J2.15, L1-15:R7.2, L1-15:R8.1, L1-15:R9.1
M16: J2.16, L1-16:R7.2, L1-16:R8.1, L1-16:R9.1
POWER:N$1: POWER:C1.1, POWER:U1.1, POWER:U2.2, POWER:U2.4
POWER:N$2: POWER:C2.1, POWER:C3.1, POWER:IC1.3, POWER:IC2.3, POWER:U1.2
POWER:N$3: POWER:IC2.1, POWER:R5.1, POWER:R6.2
POWER:N$5: POWER:IC1.1, POWER:R3.1, POWER:R4.2
POWER:N$10: POWER:R1.1, POWER:R2.2, POWER:U2.1

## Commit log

2023-02-04 Created Eagle Project Folder
2023-02-04 Add schematic and board files via upload
2023-02-16 Upload Libraries
2023-02-23 Added Enable Comparator
2023-03-12 Added files via upload
2023-03-16 removed
2023-03-16 Approved warninigs
2023-03-27 Added libraries
2023-03-29 Revert "Update README.md"
    This reverts commit 9b1e2a3aebadcbd80cac1a6ac89a990e3d6519f0.
    Fix png
2023-03-29 Revert "Added files via upload"
    This reverts commit 38fcd86d38446925b00bcede806dff6035351699.
    Fix png
2023-03-29 Fixed png
